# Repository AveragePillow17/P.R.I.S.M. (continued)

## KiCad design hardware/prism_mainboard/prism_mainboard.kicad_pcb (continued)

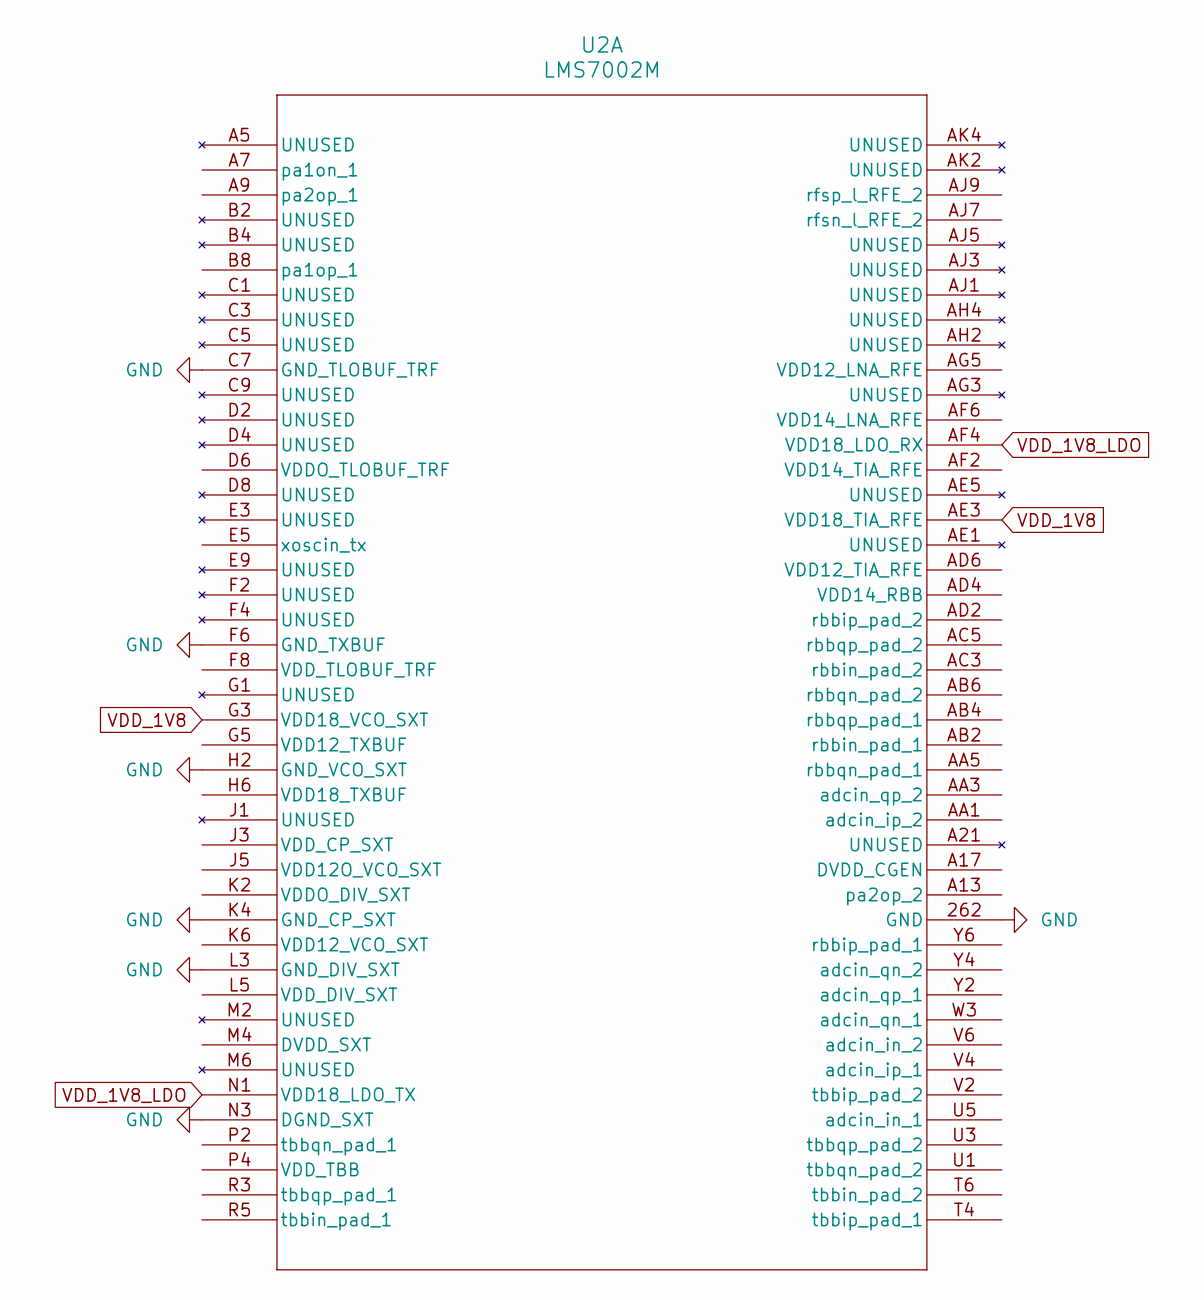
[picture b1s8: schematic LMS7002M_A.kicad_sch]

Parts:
U2: LMS7002M; AQFN261_11P5X11P5_LIM

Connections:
GND: U2.262 (GND), U2.C7 (GND_TLOBUF_TRF), U2.F6 (GND_TXBUF), U2.H2 (GND_VCO_SXT), U2.K4 (GND_CP_SXT), U2.L3 (GND_DIV_SXT), U2.N3 (DGND_SXT); also elsewhere on the board
VDD_1V8: U2.AE3 (VDD18_TIA_RFE), U2.G3 (VDD18_VCO_SXT); also elsewhere on the board
VDD_1V8_LDO: U2.AF4 (VDD18_LDO_RX), U2.N1 (VDD18_LDO_TX); also elsewhere on the board

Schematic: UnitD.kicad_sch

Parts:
U1: XC7Z015-2CLG485I; CLG485_XIL

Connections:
A0: U1.M19 (PS_DDR_A0_502); also elsewhere on the board
A1: U1.M18 (PS_DDR_A1_502); also elsewhere on the board
A2: U1.K19 (PS_DDR_A2_502); also elsewhere on the board
A3: U1.L19 (PS_DDR_A3_502); also elsewhere on the board
A4: U1.K17 (PS_DDR_A4_502); also elsewhere on the board
A5: U1.K18 (PS_DDR_A5_502); also elsewhere on the board
A6: U1.J16 (PS_DDR_A6_502); also elsewhere on the board
A7: U1.J17 (PS_DDR_A7_502); also elsewhere on the board
A8: U1.J18 (PS_DDR_A8_502); also elsewhere on the board
A9: U1.H18 (PS_DDR_A9_502); also elsewhere on the board
A10: U1.J20 (PS_DDR_A10_502); also elsewhere on the board
A12: U1.H19 (PS_DDR_A12_502); also elsewhere on the board
BA0: U1.L16 (PS_DDR_BA0_502); also elsewhere on the board
BA1: U1.L17 (PS_DDR_BA1_502); also elsewhere on the board
BA2: U1.M17 (PS_DDR_BA2_502)
CAS: U1.P20 (PS_DDR_CAS_B_502); also elsewhere on the board
CKE: U1.T19 (PS_DDR_CKE_502); also elsewhere on the board
CKN: U1.N18 (PS_DDR_CKN_502); also elsewhere on the board
CKP: U1.N19 (PS_DDR_CKP_502); also elsewhere on the board
CS: U1.P17 (PS_DDR_CS_B_502); also elsewhere on the board
DM2: U1.P22 (PS_DDR_DM2_502); also elsewhere on the board
DQL0_1: U1.M22 (PS_DDR_DQ16_502); also elsewhere on the board
DQL1_1: U1.T20 (PS_DDR_DQ17_502); also elsewhere on the board
DQL2_1: U1.N20 (PS_DDR_DQ18_502); also elsewhere on the board
DQL3_1: U1.T22 (PS_DDR_DQ19_502); also elsewhere on the board
DQL4_1: U1.R20 (PS_DDR_DQ20_502); also elsewhere on the board
DQL5_1: U1.T21 (PS_DDR_DQ21_502); also elsewhere on the board
DQL6_1: U1.M21 (PS_DDR_DQ22_502); also elsewhere on the board
DQL7_1: U1.R22 (PS_DDR_DQ23_502); also elsewhere on the board
DQSLN_1: U1.P21 (PS_DDR_DQS_N2_502); also elsewhere on the board
DQSLP_1: U1.N21 (PS_DDR_DQS_P2_502); also elsewhere on the board
DQSUN_0: U1.J21 (PS_DDR_DQS_N1_502); also elsewhere on the board
DQSUN_1: U1.W21 (PS_DDR_DQS_N3_502); also elsewhere on the board
DQSUP_0: U1.H21 (PS_DDR_DQS_P1_502); also elsewhere on the board
DQSUP_1: U1.V21 (PS_DDR_DQS_P3_502); also elsewhere on the board
DQU0_1: U1.Y20 (PS_DDR_DQ24_502); also elsewhere on the board
DQU1_1: U1.U22 (PS_DDR_DQ25_502); also elsewhere on the board
DQU2_0: U1.L22 (PS_DDR_DQ10_502); also elsewhere on the board
DQU2_1: U1.AA22 (PS_DDR_DQ26_502); also elsewhere on the board
DQU3_0: U1.L21 (PS_DDR_DQ11_502); also elsewhere on the board
DQU3_1: U1.U21 (PS_DDR_DQ27_502); also elsewhere on the board
DQU4_0: U1.L20 (PS_DDR_DQ12_502); also elsewhere on the board
DQU4_1: U1.W22 (PS_DDR_DQ28_502); also elsewhere on the board
DQU5_0: U1.K22 (PS_DDR_DQ13_502); also elsewhere on the board
DQU5_1: U1.W20 (PS_DDR_DQ29_502); also elsewhere on the board
DQU6_0: U1.J22 (PS_DDR_DQ14_502); also elsewhere on the board
DQU6_1: U1.V20 (PS_DDR_DQ30_502); also elsewhere on the board
DQU7_0: U1.K20 (PS_DDR_DQ15_502); also elsewhere on the board
DQU7_1: U1.Y22 (PS_DDR_DQ31_502); also elsewhere on the board
GND: U1.AA10 (GND), U1.AA18 (GND), U1.AB10 (GND), U1.AB15 (GND), U1.H13 (GND), U1.H15 (GND), U1.H17 (GND), U1.J10 (GND), U1.J12 (GND), U1.J14 (GND), U1.K11 (GNDADC_0), U1.K13 (GND), U1.K15 (GND), U1.K21 (GND), U1.L10 (GND), U1.L14 (GND), U1.L18 (GND), U1.M13 (GND), U1.M15 (GND), U1.N10 (GND), U1.N14 (GND), U1.N22 (GND), U1.P11 (GND), U1.P13 (GND), U1.P15 (GND), U1.P19 (GND), U1.R12 (GND), U1.R14 (GND), U1.R16 (GND), U1.T13 (GND), U1.U10 (GND), U1.U20 (GND), U1.V17 (GND), U1.W10 (GND), U1.W14 (GND), U1.Y10 (GND), U1.Y11 (GND), U1.Y21 (GND); also elsewhere on the board
ODT: U1.P18 (PS_DDR_ODT_502); also elsewhere on the board
RAS: U1.R18 (PS_DDR_RAS_B_502); also elsewhere on the board
VCCAUX: U1.K14 (VCCPAUX), U1.L13 (VCCPAUX), U1.M14 (VCCPAUX), U1.N13 (VCCAUX), U1.P12 (VCCAUX), U1.P14 (VCCPAUX), U1.R13 (VCCAUX), U1.T12 (VCCAUX); also elsewhere on the board
VCCBRAM: U1.H12 (VCCBRAM), U1.J13 (VCCBRAM)
VCCINT: U1.H14 (VCCPINT), U1.J11 (VCCINT), U1.J15 (VCCPINT), U1.K10 (VCCINT), U1.L15 (VCCPINT), U1.M10 (VCCINT), U1.N15 (VCCPINT), U1.P10 (VCCINT), U1.R15 (VCCPINT); also elsewhere on the board
VCCO_0: U1.R11 (VCCO_0); also elsewhere on the board
VCCO_DDR: U1.H22 (VCCO_DDR_502), U1.J19 (VCCO_DDR_502), U1.K16 (VCCO_DDR_502), U1.M20 (VCCO_DDR_502), U1.N17 (VCCO_DDR_502), U1.R21 (VCCO_DDR_502), U1.V22 (VCCO_DDR_502); also elsewhere on the board
WE: U1.R19 (PS_DDR_WE_B_502); also elsewhere on the board

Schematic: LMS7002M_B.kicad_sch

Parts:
U2: LMS7002M; AQFN261_11P5X11P5_LIM

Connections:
DIQ2_D0: U2.H30 (DIQ2_D0); also elsewhere on the board
DIQ2_D1: U2.J31 (DIQ2_D1); also elsewhere on the board
DIQ2_D2: U2.K30 (DIQ2_D2); also elsewhere on the board
DIQ2_D3: U2.K32 (DIQ2_D3); also elsewhere on the board
DIQ2_D4: U2.L31 (DIQ2_D4); also elsewhere on the board
DIQ2_D5: U2.K34 (DIQ2_D5); also elsewhere on the board
DIQ2_D6: U2.M30 (DIQ2_D6); also elsewhere on the board
DIQ2_D7: U2.M32 (DIQ2_D7); also elsewhere on the board
DIQ2_D8: U2.N31 (DIQ2_D8); also elsewhere on the board
DIQ2_D9: U2.N33 (DIQ2_D9); also elsewhere on the board
DIQ2_D10: U2.P30 (DIQ2_D10); also elsewhere on the board
DIQ2_D11: U2.P32 (DIQ2_D11); also elsewhere on the board
FCLK2: U2.R29 (FCLK2); also elsewhere on the board
GND: U2.B18 (DGND_CGEN), U2.B20 (GND_CP_CGEN), U2.C23 (GND_DIG), U2.C25 (VDD12_DIG), U2.D20 (GND_DIV_CGEN), U2.E25 (GND_SPI_BUF), U2.G31 (DIGPRGND2), U2.J33 (DIGPRGND1); also elsewhere on the board
LM_RST: U2.E27 (RESET); also elsewhere on the board
MCLK2: U2.P34 (MCLK2); also elsewhere on the board
SCL: U2.C27 (SCL)
SCLK: U2.C29 (SCLK); also elsewhere on the board
SDA: U2.D26 (SDA)
SDIO: U2.F30 (SDIO); also elsewhere on the board
SDO: U2.F28 (SDO); also elsewhere on the board
SEN: U2.D28 (SEN); also elsewhere on the board
VDD_1V8: U2.D16 (VDD18_TRF), U2.D24 (VDD18_DIG), U2.E17 (VDD18_BIAS), U2.E21 (VDD18_VCO_CGEN); also elsewhere on the board
VDD_1V8_DIG: U2.H32 (DIGPRVDD2); also elsewhere on the board

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
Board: 6 copper layers, 82 parts (0 on the bottom side), 140 nets, no tracks yet.

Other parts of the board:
IC3: USB3320C-EZK; QFN50P500X500X100-33N-D
J1: 503398-1892; 5033981892
J2: UJ32-21-C-H-G-HMT-LT-P24-TR; UJ3221CHGHMTLTP24TR

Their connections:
CLKOUT: IC3.1 (CLKOUT); also elsewhere on the board
DIR: IC3.31 (DIR); also elsewhere on the board
GND: J1.6 (VSS); also elsewhere on the board
NXT: IC3.2 (NXT); also elsewhere on the board
SD_CLK: J1.5 (CLK); also elsewhere on the board
SD_CMD: J1.3 (CMD); also elsewhere on the board
SD_D0: J1.7 (DAT0); also elsewhere on the board
SD_D1: J1.8 (DAT1); also elsewhere on the board
SD_D2: J1.1 (DAT2); also elsewhere on the board
SD_D3: J1.2 (CD/DAT3); also elsewhere on the board
STP: IC3.29 (STP); also elsewhere on the board
USB_D0: IC3.3 (DATA0); also elsewhere on the board
USB_D2: IC3.5 (DATA2); also elsewhere on the board
USB_D3: IC3.6 (DATA3); also elsewhere on the board
USB_D4: IC3.7 (DATA4); also elsewhere on the board
USB_D5: IC3.9 (DATA5); also elsewhere on the board
USB_D6: IC3.10 (DATA6); also elsewhere on the board
USB_D7: IC3.13 (DATA7); also elsewhere on the board

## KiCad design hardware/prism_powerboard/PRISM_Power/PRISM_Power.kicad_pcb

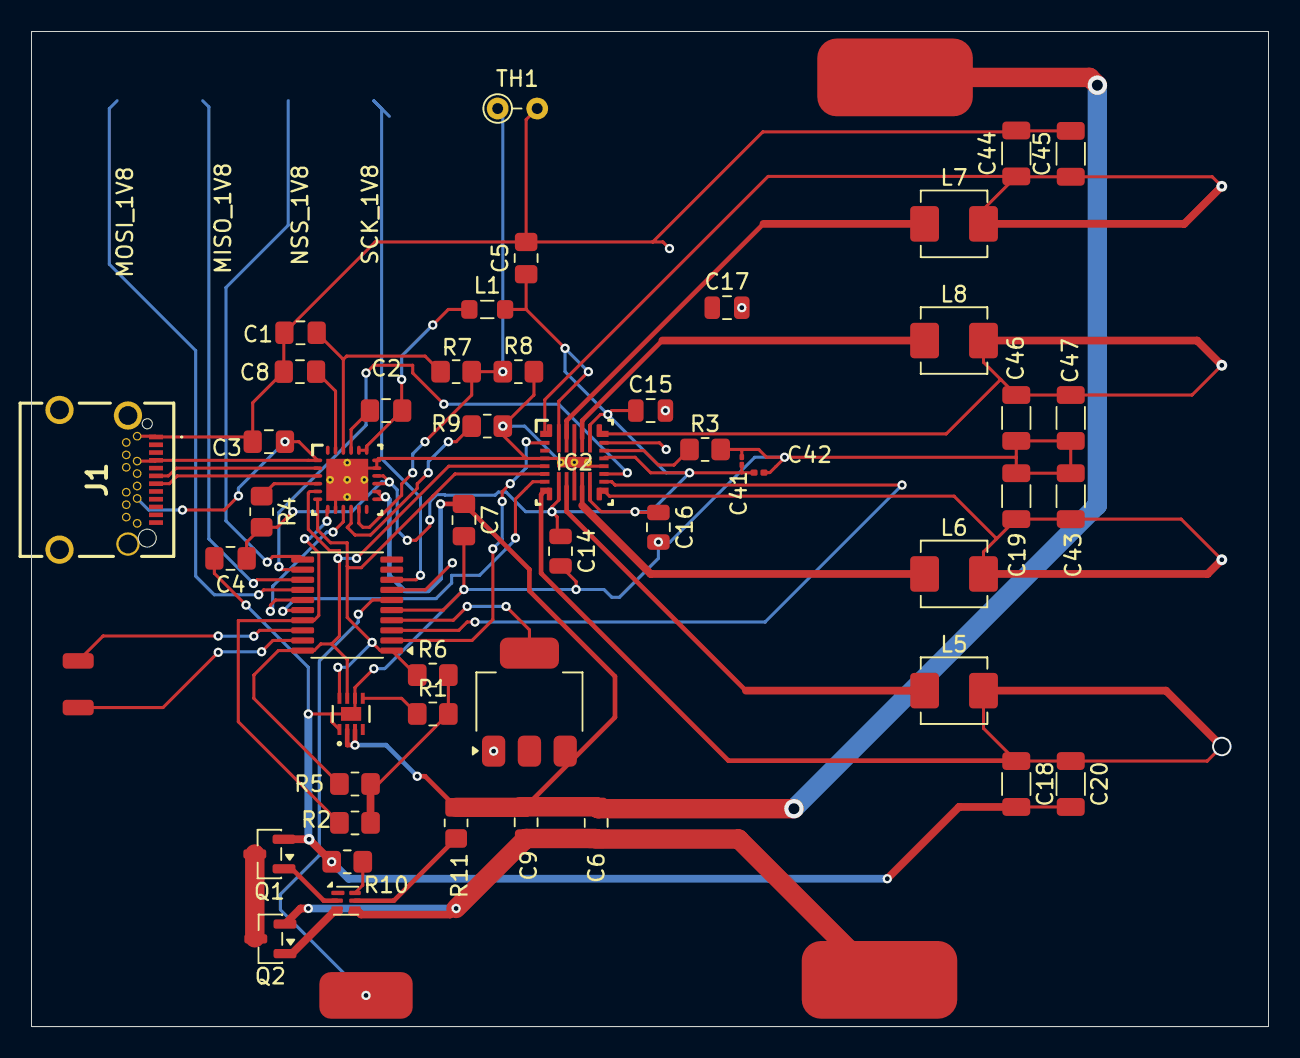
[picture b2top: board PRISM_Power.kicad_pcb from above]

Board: 2 copper layers, 79.5 x 64.0 mm, 53 parts (1 on the bottom side), 44 nets.

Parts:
C1, C6, C7: 100nF; C_0805_2012Metric_Pad1.18x1.45mm_HandSolder
C2: 47nF; C_0805_2012Metric_Pad1.18x1.45mm_HandSolder
C3: 1uF; C_0805_2012Metric_Pad1.18x1.45mm_HandSolder
C4, C5, C9: 10uF; C_0805_2012Metric_Pad1.18x1.45mm_HandSolder
C8: 4.7uF; C_0805_2012Metric_Pad1.18x1.45mm_HandSolder
C14, C15, C16, C17: 10uF; C_0805_2012Metric
C18, C19, C44, C46: 22uF; C_1206_3216Metric
C20, C43, C45, C47: 47uF; C_1206_3216Metric
C41: 100nF; C_01005_0402Metric
C42: 100nF; C_0201_0603Metric
IC2: LP87564WRNFTQ1; RNF0026C
J1: UJ32-21-C-H-G-HMT-LT-P24-TR; UJ3221CHGHMTLTP24TR
L1: 2.2uH; L_0805_2012Metric_Pad1.05x1.20mm_HandSolder
L5, L6, L7, L8: 0.47uH; L_Vishay_IHLP-1616
MISO_1V8: (no value)
MOSI_1V8: SolderWirePad_1x01_SMD_4x8mm
NSS_1V8: (no value)
Q1, Q2: AO3400A; SOT-23
R1, R2, R3, R4, R5, R6: 10k; R_0805_2012Metric_Pad1.20x1.40mm_HandSolder
R7: 5.23k; R_0805_2012Metric_Pad1.20x1.40mm_HandSolder
R8: 30.1k; R_0805_2012Metric_Pad1.20x1.40mm_HandSolder
R9: 260; R_0805_2012Metric_Pad1.20x1.40mm_HandSolder
R10: 2.2k; R_0805_2012Metric_Pad1.20x1.40mm_HandSolder
R11: 330; R_0805_2012Metric_Pad1.20x1.40mm_HandSolder
SCK_1V8: (no value)
TH1: Thermistor_NTC_10k; R_Axial_DIN0204_L3.6mm_D1.6mm_P2.54mm_Vertical
U1: STM32G031F6Px; TSSOP-20_4.4x6.5mm_P0.65mm
U2: BQ25895RTW; RTW0024H
U3: BQ297xy; WSON-6_1.5x1.5mm_P0.5mm
U4: MAX17048G+T10; 21-0168E_T822-3_MXM
U5: AMS1117-1.8; SOT-223-3_TabPin2

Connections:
+1V8: R1.2, R2.1, R5.2, R6.2
+BATT: C6.1, C7.1, C9.1, R11.1, U2.13 (BAT), U2.14 (BAT), U4.2 (CELL), U4.3 (VDD), U5.3 (VI)
-BATT: C6.2, C9.2, Q2.2 (S), U3.4 (VSS), U4.4 (GND)
ALRT_GAUGE: R1.1, U4.5 (*ALRT)
CE_CHRG: U1.15 (PA8/PB0/PB1/PB2), U2.9 (~CE)
EN1: IC2.7 (EN1), U1.16 (PA9/PA11)
EN2: IC2.15 (EN2), U1.3 (PC15)
EN3: IC2.2 (EN3), U1.2 (PB9/PC14)
FB_B0: C18.1, C20.1, IC2.8 (FB_B0_1), L5.2
FB_B1: C19.1, C43.1, IC2.14 (FB_B1_1), L6.2
FB_B2: C44.1, C45.1, IC2.1 (FB_B2_1), L7.2
FB_B3: C46.1, C47.1, IC2.21 (FB_B3_1), L8.2
GND: C1.1, C3.1, C4.2, C5.2, C7.2, C8.2, C14.2, C15.2, C16.2, C17.2, C18.2, C19.2, C20.2, C41.2, C42.2, C43.2, C44.2, C45.2, C46.2, C47.2, IC2.4 (AGND_1), IC2.11 (PGND_B01), IC2.17 (AGND_2), IC2.24 (PGND_B23), IC2.27, IC2.V, J1.A1 (GND_1), J1.B1 (GND_3), J1.B12 (GND_4), Q1.2 (S), R3.2, R8.2, R9.2, R10.2, TH1.2, U1.5 (VSS), U2.8 (OTG), U2.17 (PGND), U2.18 (PGND), U2.25 (PGND), U2.V, U4.1 (CTG), U4.6 (QSTRT), U4.9 (EPAD), U5.1 (GND)
I2C_SCL_1V8: IC2.5 (SCL), R5.1, U1.20 (PB3/PB4/PB5/PB6), U2.5 (SCL), U4.7 (SCL)
I2C_SDA_1V8: IC2.6 (SDA), R6.1, U1.1 (PB7/PB8), U2.6 (SDA), U4.8 (SDA)
INT_CHRG: R2.2, U1.17 (PA10/PA12), U2.7 (~INT)
unnamed: C2.2, L1.1, U2.19 (SW), U2.20 (SW)
unnamed: IC2.19 (NINT), R3.1
unnamed: Q1.3 (D), Q2.3 (D)
unnamed: Q1.1 (G), U3.2 (Cout)
unnamed: Q2.1 (G), U3.3 (Dout)
unnamed: U1.4 (VDD), U5.2 (VO)
unnamed: C2.1, U2.21 (BTST)
unnamed: R9.1, U2.10 (ILIM)
unnamed: C1.2, U2.23 (PMID)
unnamed: C8.1, R7.1, U2.22 (REGN)
unnamed: R7.2, R8.1, TH1.1, U2.11 (TS)
unnamed: R11.2, U3.5 (BAT)
unnamed: R10.1, U3.6 (V-)
PGD_S: IC2.16 (PGOOD), U1.12 (PA5)
PMIC_RST: IC2.20 (NRST), U1.7 (PA0)
SPI_MISO_1V8: MISO_1V8.1, U1.13 (PA6)
SPI_MOSI_1V8: MOSI_1V8.1, U1.14 (PA7)
SPI_NSS_1V8: NSS_1V8.1, U1.11 (PA4)
SPI_SCK_1V8: SCK_1V8.1, U1.8 (PA1)
STAT_CHG: R4.1, U2.4 (STAT)
SW_B1: IC2.12 (SW_B1), L6.1
SW_B2: IC2.25 (SW_B2), L7.1
SW_B3: IC2.23 (SW_B3), L8.1
SW__B0: IC2.10 (SW_B0), L5.1
SYS_3V5: C4.1, C5.1, C14.1, C15.1, C16.1, C17.1, C41.1, C42.1, IC2.9 (VIN_B0), IC2.13 (VIN_B1), IC2.18 (VANA), IC2.22 (VIN_B3), IC2.26 (VIN_B2), L1.2, R4.2, U2.15 (SYS), U2.16 (SYS)
USB_D_Minus: J1.A7 (DN1), U2.3 (D-)
USB_D_Plus: J1.A6 (DP1), U2.2 (D+)
USB_VCC: C3.2, J1.A4 (VBUS_1), J1.B4 (VBUS_3), J1.B9 (VBUS_4), U2.1 (VBUS)

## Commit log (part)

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2026-05-11 Docs
    This is just mostly the docs and sources for learning, very large files
2026-05-11 Create .gitignore
    Create .gitignore and ignore files aboce 100MB
2026-05-11 Some More Files
    Block Diagram, Schedule Excel Sheet, completed
2026-05-17 Document Updates
    Schematics and Hardware updates
2026-05-17 KiCAD and Datasheet Updates
    Updated KiCAD added LMS7002M Transceiver, added power systems sheet, added LMS7002M Datasheets and PCB sheet for XC7Z010
2026-05-18 KiCAD Update
    Added Power System Schematics. Decided on a 4 in 1 Buck and LDO, LP87222TQ1, for 3.3V and 1.8V LDO, and 1.8V and 1.0V Buck converter.
2026-05-20 Schematics
    More schematics updates, moving to Desktop for editing. Continued with power usage, debating use of Dedicated DDR3/3L power IC instead of using LDO and Buck from mainboard power.
2026-05-23 Protoflow add
    Some testing with Protoflow for the schematic layout
2026-05-23 More Protoflow
    Power Systesm
2026-05-24 Removed Protoflow
    Removed protoflow because it has not advanced enough to help in any substantial way, going back to KiCAD
2026-05-25 Datasheets
    Added a few datasheets and new device datasheets
2026-05-25 Update .gitignore
    Ignore all .lck files, causing issues on saving
2026-05-25 Update .gitignore
    Also ignoring .kicad_prl files
2026-05-29 Power System Schematics
    Updated Power System Schematics, changed the power supply IC from 2 Buck 2 LDO to 4 Buck and include 2 LDO to provide Low Noise power to RF and sensitive circuitry
2026-06-13 Reschedule
    Made a more accurate schedule based off workload and realism
